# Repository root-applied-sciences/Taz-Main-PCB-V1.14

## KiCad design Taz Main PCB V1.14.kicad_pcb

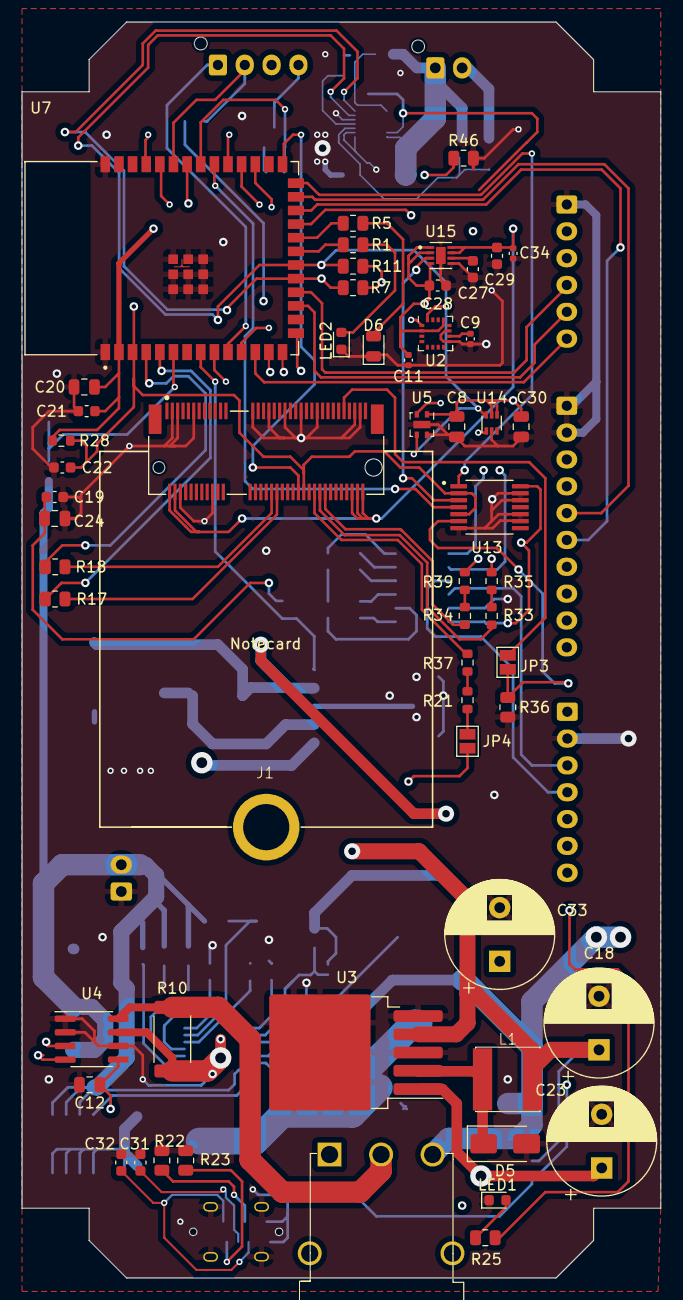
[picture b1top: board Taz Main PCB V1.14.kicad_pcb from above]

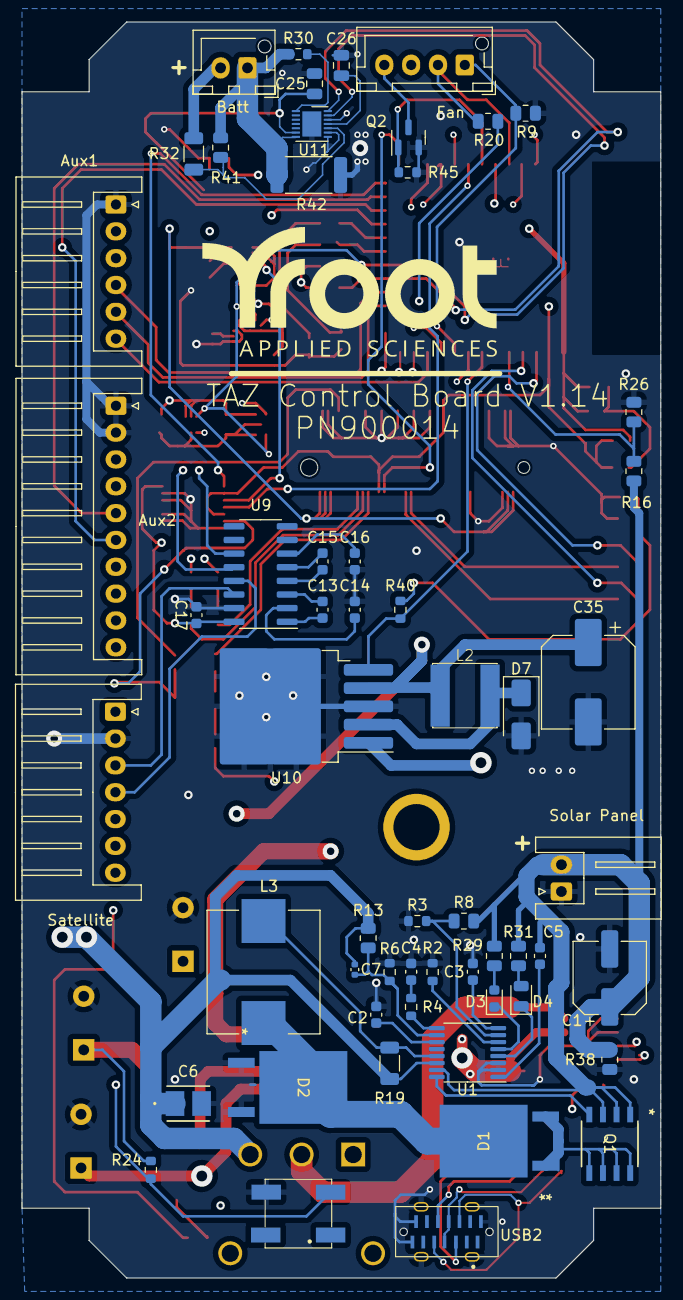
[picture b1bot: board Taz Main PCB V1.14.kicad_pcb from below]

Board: 4 copper layers, 59.5 x 117.0 mm, 113 parts (57 on the bottom side), 90 nets.

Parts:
C1: 47µF; CP_Elec_6.3x7.7
C2, C5, C13, C14, C15, C16, C17, C19, C21, C29: 100nF; C_0603_1608Metric
C3: 470pF; C_0603_1608Metric
C4: 220nF; C_0603_1608Metric
C6: 10µF; CAP_TR3B_VIS-M
C7: 2pF; C_0402_1005Metric
C8, C12, C25, C30: 100nF; C_0805_2012Metric
C9, C34: 4.7µF; C_0402_1005Metric
C11: 100nF; C_0402_1005Metric
C18: 470µF; CP_Radial_D10.0mm_P5.00mm
C20, C24: 10µF; C_0805_2012Metric
C22, C28: 1µF; C_0603_1608Metric
C23, C33: 680µF; CP_Radial_D10.0mm_P5.00mm
C26: 0.47µF; C_0805_2012Metric
C27: 1nF; C_0603_1608Metric
C31, C32: 22pF; C_0603_1608Metric
C35: 220µF; CP_Elec_8x10.5
CN1: Solar Panel; JST_XH_S2B-XH-A_1x02_P2.50mm_Horizontal
CN2: Auxilary Conn; JST_XH_S6B-XH-A_1x06_P2.50mm_Horizontal
CN3: Aux Conn 2; JST_XH_S10B-XH-A_1x10_P2.50mm_Horizontal
CN4: APCI0136-P001A; TE_2199119-4
CN5: RS232 Conn; JST_XH_S7B-XH-A_1x07_P2.50mm_Horizontal
D1, D2: 50WQ03FN; DPAK_VIS
D3: Green; LED_0603_1608Metric
D4, D6: Red; LED_0805_2012Metric
D5, D7: RB050L-60TE25; D_SMA
J1: Screw_Terminal_01x01; Round nut stand off
JP3, JP4: SolderJumper; SolderJumper-2_P1.3mm_Open_Pad1.0x1.5mm
L1, L2: 33µH; RootSMD Power Inductors
L3: 15µH; L_Sunlord_MWSA1004S
LED1: Blue; LED_0603_1608Metric
LED2: Green; LED_0603_1608Metric
Q1: AO4459; SO8_SOP-8L_AOS
Q2: IRLML6244; SOT-23
R1, R17, R18, R25: 100Ω; R_0805_2012Metric
R2, R30: 10kΩ NTC; R_0603_1608Metric
R3: 13.7kΩ; R_0603_1608Metric
R4: 120Ω; R_0603_1608Metric
R5: 243Ω; R_0805_2012Metric
R6: 68kΩ; R_0603_1608Metric
R7, R9, R11, R20, R36: 4.7kΩ; R_0805_2012Metric
R8: 255kΩ; R_0805_2012Metric
R10: 0.1Ω; R_2512_6332Metric
R13: 340kΩ; R_0805_2012Metric
R16: 33.2kΩ; R_0805_2012Metric
R19: 66mΩ; R_1206_3216Metric
R21, R33, R34, R35, R37, R39: 100Ω; R_0603_1608Metric
R22, R23: 5.1kΩ; R_0805_2012Metric
R24, R28, R40, R45: 10kΩ; R_0603_1608Metric
R26: 4.99kΩ; R_0805_2012Metric
R29, R31: 2.2kΩ; R_0805_2012Metric
R32: 1.8MΩ; R_1206_3216Metric
R38: 20kΩ; R_0805_2012Metric
R41: 200kΩ; R_0805_2012Metric
R42: 10mΩ; R_2512_6332Metric
R46: 100kΩ; R_0805_2012Metric
SW1: 500ASSP1M6QE; SW_500ASSP1M6QE
SW2: Telemitry Switch; 430182043816
U1: CN3722; TSSOP-16_4.4x5mm_P0.65mm
U2: QMC5883P; LGA-16_3x3mm_P0.5mm
U3: LM2596R-3.3; TO-263-5_TabPin3
U4: INA219AxD; SOIC-8_3.9x4.9mm_P1.27mm
U5: ENS210-LQFM; AMS_QFN-4-1EP_2x2mm_P0.95mm_EP0.7x1.6mm
U6: Battery Socket; JST_XH_B2B-XH-AM_1x02_P2.50mm_Vertical
U7: ESP32-S3-WROOM-1-N8R2; XCVR_ESP32-S3-WROOM-1-N8R2
U8: Fan Connector; JST_XH_B4B-XH-AM_1x04_P2.50mm_Vertical
U9: MAX3232; SOIC-16_3.9x9.9mm_P1.27mm
U10: LM2596R-5.0; TO-263-5_TabPin3
U11: MAX17261xxTD; TDFN-14-1EP_3x3mm_P0.4mm_EP1.78x2.35mm
U13: SN74LVC08APWR; SOP65P640X120-14N
U14: TMP102AIDRLR; SOT-563
U15: TPS22965DSGR; SON50P200X200X80-9N
USB2: GT-USB-7090C; GTUSB7090

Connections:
+3V3: C8.1, C11.1, C12.1, C17.1, C18.1, C19.1, C20.1, C21.1, C24.1, C25.1, C28.1, C30.1, CN2.2, CN3.8, JP4.1 (A), L1.2, R7.1, R11.1, R20.1, R24.1, R28.1, R40.1, U2.2 (VDD), U3.4 (FB), U4.5 (VS), U5.1 (VDD), U7.2 (3V3), U9.16 (VCC), U11.6 (BATT), U13.14 (VCC), U14.4 (ADD0), U14.5 (V+), U15.1 (VIN), U15.2 (VIN__1), U15.4 (VBIAS)
+5V: C35.1, CN3.9, L2.2, U10.4 (FB)
/Aux Connector/12V_System: C23.1, C33.1, CN2.3, CN3.10, CN5.5, R10.2, U3.1 (VIN), U4.7 (IN-), U8.3, U10.1 (VIN)
/Aux Connector/Aux1-1: CN2.6, U7.12 (IO8)
/Aux Connector/Aux1-2: CN2.5, U7.17 (IO9)
/Aux Connector/Aux1-3: CN2.4, U7.18 (IO10)
/Aux Connector/Aux2-1: CN3.7, U7.34 (IO41)
/Aux Connector/Aux2-2: CN3.6, U7.24 (IO47)
/Aux Connector/Aux2-3: CN3.5, U7.25 (IO48)
/Aux Connector/ESP32RX: U7.31 (IO38), U9.12 (R1OUT)
/Aux Connector/ESP32TX: U7.30 (IO37), U9.11 (T1IN)
/Aux Connector/Iridiumon/off: CN5.6, U7.9 (IO16)
/Aux Connector/NetworkAvailable: CN5.7, U7.29 (IO36)
/Aux Connector/PowerDetect: CN5.1, U7.11 (IO18)
/Aux Connector/SCL: CN3.4, R7.2, U2.1 (SCL), U4.4 (SCL), U5.2 (SCL), U7.19 (IO11), U11.14 (SCL), U14.1 (SCL)
/Aux Connector/SDA: CN3.3, R11.2, U2.16 (SDA), U4.3 (SDA), U5.3 (SDA), U7.20 (IO12), U11.13 (SDA), U14.6 (SDA)
/BlueStatus: R25.2, U7.23 (IO21)
/FANCTRLPWM: R20.2, U7.35 (IO42), U8.2
/FANSpeedMeasure: R9.1, U7.10 (IO17), U8.1
/FanEnable: Q2.1 (G), R45.2, U7.33 (IO40)
/MCU_RST: C22.1, CN4.52, R28.2, R46.1, U7.3 (EN), U13.2 (1B), U13.5 (2B)
/Notecard Connection/MCU_BOOT: CN4.50, U7.27 (IO0)
/Notecard Connection/SCL_NC: R18.2, U7.4 (IO4)
/Notecard Connection/SDA_NC: R17.2, U7.5 (IO5)
/Notecard Connection/notecard_auxRX: R35.2, U7.37 (TXD0)
/Notecard Connection/notecard_auxTX: R39.2, U7.36 (RXD0)
/Onboard sensors/GreenStatus: R1.2, U7.21 (IO13)
/Onboard sensors/RedStatus: R5.2, U7.22 (IO14)
/Power Monitoring/12V_Power: C6.1, C7.1, R13.1, R19.1, R32.1, SW1.3, U1.14 (BAT), U6.2
/Power Monitoring/12V_SystemIN: R10.1, SW1.2, U4.8 (IN+)
/Power Monitoring/ADCSolarVoltage: R16.2, R26.1, U7.6 (IO6)
/Power Monitoring/PV+: C1.1, C5.1, CN1.2, Q1.1 (S), Q1.2 (S), Q1.3 (S), R8.1, R16.1, R29.1, R31.1, R38.1, U1.15 (VCC)
/Solar Charging Control/5VEnable: R40.2, U7.8 (IO15), U10.5 (ON/OFF)
/USB_Connector/USBD+: C31.1, U7.14 (IO20), USB2.A6 (DP1), USB2.B6 (DP2)
/USB_Connector/USBD-: C32.1, U7.13 (IO19), USB2.A7 (DN1), USB2.B7 (DN2)
/notecard_RST: U7.32 (IO39), U13.4 (2A)
/notecard_Vcc: U7.26 (IO45), U13.1 (1A)
GND: C1.2, C2.2, C3.2, C4.2, C6.2, C8.2, C9.2, C11.2, C12.2, C14.2, C16.2, C17.2, C18.2, C19.2, C20.2, C21.2, C22.2, C23.2, C24.2, C25.2, C26.2, C27.2, C28.2, C29.2, C30.2, C31.2, C32.2, C33.2, C34.2, C35.2, CN1.1, CN2.1, CN3.1, CN3.2, CN4.3, CN4.5, CN4.6, CN4.11, CN4.18, CN4.33, CN4.39, CN4.45, CN4.51, CN4.57, CN4.71, CN4.73, CN5.2, D2.1, D2.3, D5.2 (A), D6.1 (K), D7.2 (A), LED1.1 (K), LED2.1 (K), Q2.2 (S), R2.2, R3.2, R6.2, R9.2, R22.2, R23.2, R26.2, R36.2, R38.2, R42.2, R45.1, R46.2, SW2.4, U1.2 (PGND), U1.3 (GND), U2.9 (GND), U2.11 (GND), U3.3 (GND), U3.5 (ON/OFF), U4.1 (A1), U4.2 (A0), U4.6 (GND), U5.4 (GND), U5.5 (GND), U7.1 (GND), U7.40 (GND__1), U7.41_1 (GND__2), U7.41_2 (GND__3), U7.41_3 (GND__4), U7.41_4 (GND__5), U7.41_5 (GND__6), U7.41_6 (GND__7), U7.41_7 (GND__8), U7.41_8 (GND__9), U7.41_9 (GND__10), U9.15 (GND), U10.3 (GND), U11.8 (GND), U11.9 (CSPL), U11.12 (ALRT), U11.15 (GND), U13.7 (GND), U13.9 (3A), U13.10 (3B), U13.12 (4A), U13.13 (4B), U14.2 (GND), U15.5 (GND), U15.9 (GND__1), USB2.A1 (GND), USB2.A12 (GND__1), USB2.B12 (GND__3), USB2.SH1 (SHIELD), USB2.SH2 (SHIELD__1), USB2.SH3 (SHIELD__2), USB2.SH4 (SHIELD__3)
NCEnable: U13.3 (1Y), U15.3 (ON)
NCReset: JP3.1 (A), R36.1, U13.6 (2Y)
NCVcc: C29.1, C34.1, CN4.2, CN4.4, CN4.70, CN4.72, CN4.74, U15.7 (VOUT), U15.8 (VOUT__1)
unnamed: C4.1, R4.2
unnamed: CN4.40, R18.1
unnamed: CN4.42, R17.1
unnamed: CN4.56, R37.1
unnamed: CN4.58, R33.1
unnamed: CN4.60, R34.1
unnamed: D1.1, D1.3, Q1.5 (D), Q1.6 (D), Q1.7 (D), Q1.8 (D)
unnamed: D1.2, D2.2, L3.2
unnamed: D3.2 (A), R29.2
unnamed: D3.1 (K), U1.5 (DONE#)
unnamed: D4.2 (A), R31.2
unnamed: D4.1 (K), U1.4 (CHRG#)
unnamed: D5.1 (K), L1.1, U3.2 (VOUT)
unnamed: D6.2 (A), R5.1
unnamed: D7.1 (K), L2.1, U10.2 (VOUT)
unnamed: CN4.67, JP3.2 (B)
unnamed: JP4.2 (B), R21.2
unnamed: LED1.2 (A), R25.1
unnamed: LED2.2 (A), R1.1
unnamed: Q1.4 (G), U1.16 (DRV)
unnamed: Q2.3 (D), U8.4
unnamed: R21.1, R37.2
unnamed: R33.2, R35.1
unnamed: R34.2, R39.1
unnamed: C3.1, U1.8 (COM1)
unnamed: R4.1, U1.9 (COM2)
unnamed: C2.1, U1.11 (COM3)
unnamed: L3.1, R19.2, U1.13 (CSP)
unnamed: C7.2, R6.1, R13.2, U1.10 (FB)
unnamed: R3.1, R8.2, U1.7 (MPPT)
unnamed: R2.1, U1.6 (TEMP)
unnamed: C5.2, U1.1 (VG)
unnamed: C9.1, U2.10 (C1)
unnamed: C13.1, U9.1 (C1+)
unnamed: C13.2, U9.3 (C1-)
unnamed: C15.1, U9.4 (C2+)
unnamed: C15.2, U9.5 (C2-)
unnamed: C14.1, U9.2 (VS+)
unnamed: C16.1, U9.6 (VS-)
unnamed: R32.2, R41.1, U11.10 (CELLX)
unnamed: R30.2, R41.2, R42.1, U6.1, U11.7 (CSN)
unnamed: C26.1, U11.11 (REG)
unnamed: R30.1, U11.1 (TH)
unnamed: C27.1, U15.6 (CT)
unnamed: R22.1, USB2.A5 (CC1)
unnamed: R23.1, USB2.B5 (CC2)
RS232_RX: CN5.3, U9.14 (T1OUT)
RS232_TX: CN5.4, U9.13 (R1IN)
TelemetryButton: R24.2, SW2.3, U7.15 (IO3)

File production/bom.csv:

Designator,Footprint,Quantity,Value,LCSC Part #
C1,CP_Elec_6.3x7.7,1,47µF,C3349
C11,0402,1,100nF,C307331
"C12, C25, C30, C8",0805,4,100nF,C49678
"C13, C14, C15, C16, C17, C19, C2, C21, C29, C5",0603,10,100nF,C14663
C18,CP_Radial_D10.0mm_P5.00mm,1,470µF,C88732
"C20, C24",0805,2,10µF,C2932476
"C22, C28",0603,2,1µF,C5673
"C23, C33",CP_Radial_D10.0mm_P5.00mm,2,680µF,C357636
C26,0805,1,0.47µF,C13967
C27,0603,1,1nF,C100040
C3,0603,1,470pF,C1620
"C31, C32",0603,2,22pF,C105620
"C34, C9",0402,2,4.7µF,C23733
C35,CP_Elec_8x10.5,1,220µF,C4747976
C4,0603,1,220nF,C21120
C6,CAP_TR3B_VIS-M,1,10µF,C128259
C7,0402,1,2pF,C1558
CN1,JST_XH_S2B-XH-A_1x02_P2.50mm_Horizontal,1,Solar Panel,C33132
CN2,JST_XH_S6B-XH-A_1x06_P2.50mm_Horizontal,1,Auxilary Conn,C2908615
CN3,JST_XH_S10B-XH-A_1x10_P2.50mm_Horizontal,1,Aux Conn 2,C491718
CN4,TE_2199119-4,1,APCI0136-P001A,C841670
CN5,JST_XH_S7B-XH-A_1x07_P2.50mm_Horizontal,1,RS232 Conn,C2908616
"D1, D2",DPAK_VIS,2,50WQ03FN,C222476
D3,0603,1,Green,C72043
"D4, D6",0805,2,Red,C84256
"D5, D7",D_SMA,2,RB050L-60TE25,C209642
J1,Round nut stand off,1,Screw_Terminal_01x01,C7528082
"JP3, JP4",SolderJumper-2_P1.3mm_Open_Pad1.0x1.5mm,2,SolderJumper,
"L1, L2",RootSMD Power Inductors,2,33µH,C497840
L3,L_Sunlord_MWSA1004S,1,15µH,C475916
LED1,0603,1,Blue,C2288
LED2,0603,1,Green,C12624
Q1,SO8_SOP-8L_AOS,1,AO4459,C49047
Q2,SOT-23,1,IRLML6244,C143946
"R1, R17, R18, R25",0805,4,100Ω,C17408
R10,2512,1,0.1Ω,C2960832
"R11, R20, R36, R7, R9",0805,5,4.7kΩ,C60816
R13,0805,1,340kΩ,C269564
R16,0805,1,33.2kΩ,C3016779
R19,1206,1,66mΩ,C2988665
"R2, R30",0603,2,10kΩ NTC,C25804
"R21, R33, R34, R35, R37, R39",0603,6,100Ω,C22775
"R22, R23",0805,2,5.1kΩ,C27834
"R24, R28, R40, R45",0603,4,10kΩ,C25804
R26,0805,1,4.99kΩ,C17677
"R29, R31",0805,2,2.2kΩ,C17520
R3,0603,1,13.7kΩ,C203293
R32,1206,1,1.8MΩ,C2933615
R38,0805,1,20kΩ,C114566
R4,0603,1,120Ω,C22787
R41,0805,1,200kΩ,C2907238
R42,2512,1,10mΩ,C105366
R46,0805,1,100kΩ,C149504
R5,0805,1,243Ω,C5159715
R6,0603,1,68kΩ,C163940
R8,0805,1,255kΩ,C3016493
SW1,SW_500ASSP1M6QE,1,500ASSP1M6QE,C2884775
SW2,430182043816,1,Telemitry Switch,C495902
U1,TSSOP-16_4.4x5mm_P0.65mm,1,CN3722,C77905
U10,TO-263-5_TabPin3,1,LM2596R-5.0,C77782
U11,TDFN-14-1EP_3x3mm_P0.4mm_EP1.78x2.35mm,1,MAX17261xxTD,C7457893
U13,SOP65P640X120-14N,1,SN74LVC08APWR,C465737
U14,SOT-563,1,TMP102AIDRLR,C99269
U15,SON50P200X200X80-9N,1,TPS22965DSGR,C122837
U2,LGA-16_3x3mm_P0.5mm,1,QMC5883P,C2847467
U3,TO-263-5_TabPin3,1,LM2596R-3.3,C90690
U4,SOIC-8_3.9x4.9mm_P1.27mm,1,INA219AxD,C138706
U5,AMS_QFN-4-1EP_2x2mm_P0.95mm_EP0.7x1.6mm,1,ENS210-LQFM,C2991202
U6,JST_XH_B2B-XH-AM_1x02_P2.50mm_Vertical,1,Battery Socket,C2908600
U7,XCVR_ESP32-S3-WROOM-1-N8R2,1,ESP32-S3-WROOM-1-N8R2,C2913204
U8,JST_XH_B4B-XH-AM_1x04_P2.50mm_Vertical,1,Fan Connector,C161871
U9,SOIC-16_3.9x9.9mm_P1.27mm,1,MAX3232,C18261
USB2,GTUSB7090,1,GT-USB-7090C,C3019716

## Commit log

2026-01-06 initial file upload
2026-01-23 Updated with PDF
